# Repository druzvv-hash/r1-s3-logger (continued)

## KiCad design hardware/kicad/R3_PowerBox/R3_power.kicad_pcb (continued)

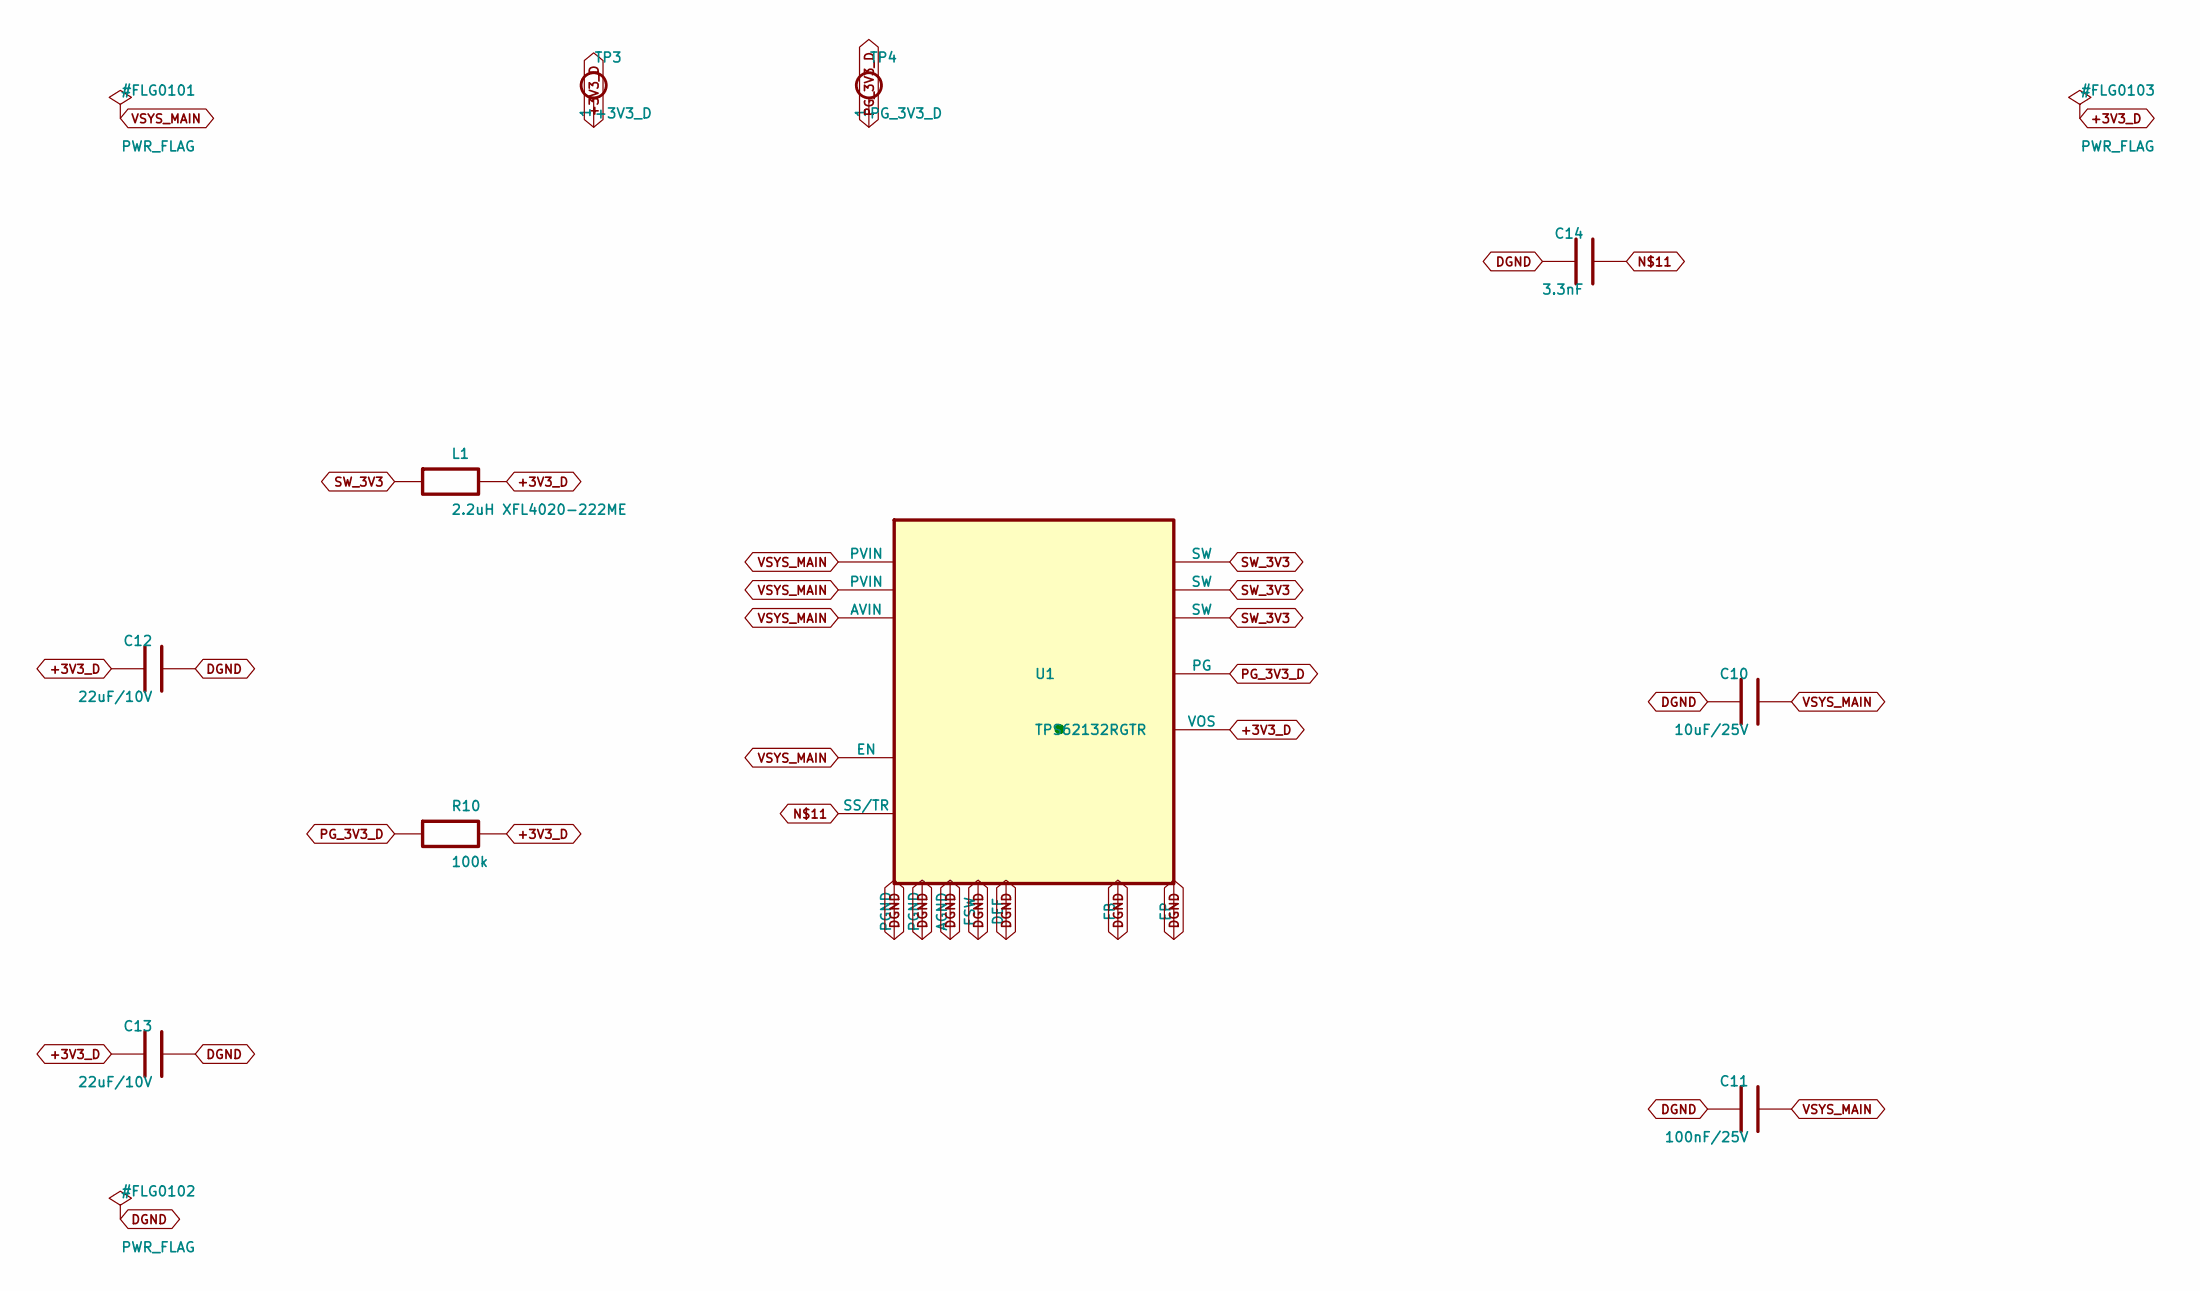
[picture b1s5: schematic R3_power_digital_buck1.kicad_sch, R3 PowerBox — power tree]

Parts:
C10: 10uF/25V; C_1206_3216Metric
C11: 100nF/25V; C_0603_1608Metric
C12, C13: 22uF/10V; C_0805_2012Metric
C14: 3.3nF; C_0603_1608Metric
L1: 2.2uH XFL4020-222ME; L_Coilcraft_XFL4020
R10: 100k; R_0603_1608Metric
TP3: +3V3_D; TestPoint_Plated_Hole_D2.0mm
TP4: PG_3V3_D; TestPoint_Plated_Hole_D2.0mm
U1: TPS62132RGTR; VQFN-16-1EP_3x3mm_P0.5mm_EP1.45x1.45mm

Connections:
+3V3_D: C12.1, C13.1, L1.2, R10.2, TP3.1, U1.14 (VOS); also elsewhere on the board
DGND: C10.2, C11.2, C12.2, C13.2, C14.2, U1.5 (FB), U1.6 (AGND), U1.7 (FSW), U1.8 (DEF), U1.15 (PGND), U1.16 (PGND), U1.17 (EP); also elsewhere on the board
unnamed: C14.1, U1.9 (SS/TR)
PG_3V3_D: R10.1, TP4.1, U1.4 (PG); also elsewhere on the board
SW_3V3: L1.1, U1.1 (SW), U1.2 (SW), U1.3 (SW)
VSYS_MAIN: C10.1, C11.1, U1.10 (AVIN), U1.11 (PVIN), U1.12 (PVIN), U1.13 (EN); also elsewhere on the board

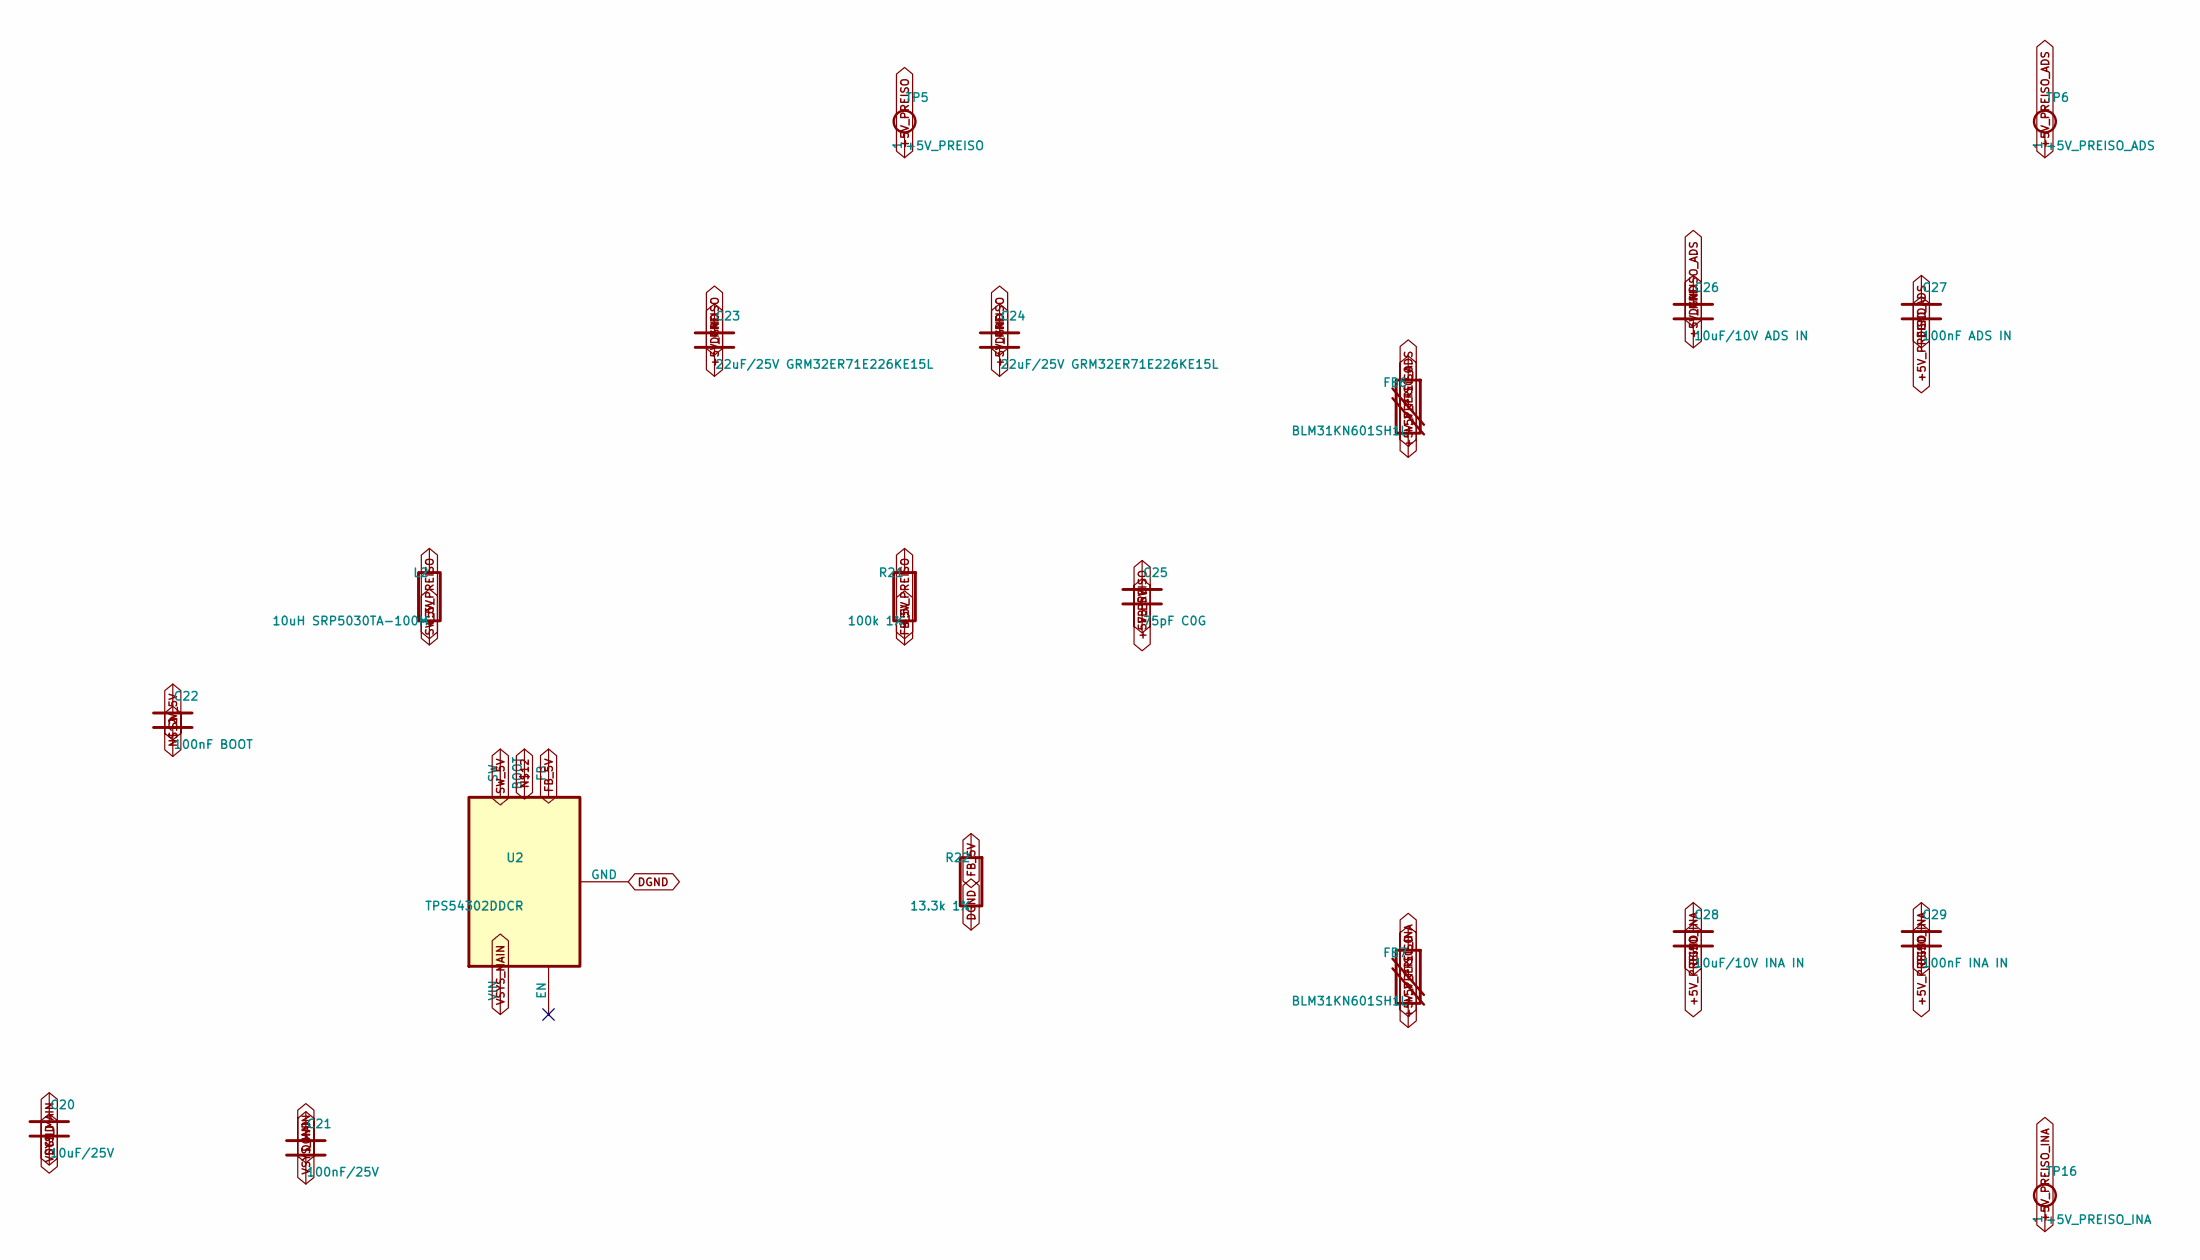
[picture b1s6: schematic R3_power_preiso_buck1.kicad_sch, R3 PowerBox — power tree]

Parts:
C20: 10uF/25V; C_1206_3216Metric
C21: 100nF/25V; C_0603_1608Metric
C22: 100nF BOOT; C_0603_1608Metric
C23, C24: 22uF/25V GRM32ER71E226KE15L; C_1210_3225Metric
C25: 75pF C0G; C_0603_1608Metric
C26: 10uF/10V ADS IN; C_0805_2012Metric
C27: 100nF ADS IN; C_0603_1608Metric
C28: 10uF/10V INA IN; C_0805_2012Metric
C29: 100nF INA IN; C_0603_1608Metric
FB6, FB7: BLM31KN601SH1L; L_1206_3216Metric_Pad1.22x1.90mm_HandSolder
L2: 10uH SRP5030TA-100M; L_Bourns_SRP5030T
R21: 100k 1%; R_0603_1608Metric
R22: 13.3k 1%; R_0603_1608Metric
TP5: +5V_PREISO; TestPoint_Plated_Hole_D2.0mm
TP6: +5V_PREISO_ADS; TestPoint_Plated_Hole_D2.0mm
TP16: +5V_PREISO_INA; TestPoint_Plated_Hole_D2.0mm
U2: TPS54302DDCR; SOT-23-6

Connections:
+5V_PREISO: C23.1, C24.1, C25.1, FB6.1, FB7.1, L2.2, R21.1, TP5.1
+5V_PREISO_ADS: C26.1, C27.1, FB6.2, TP6.1; also elsewhere on the board
+5V_PREISO_INA: C28.1, C29.1, FB7.2, TP16.1; also elsewhere on the board
DGND: C20.2, C21.2, C23.2, C24.2, C26.2, C27.2, C28.2, C29.2, R22.2, U2.1 (GND); also elsewhere on the board
FB_5V: C25.2, R21.2, R22.1, U2.4 (FB)
unnamed: C22.1, U2.6 (BOOT)
SW_5V: C22.2, L2.1, U2.2 (SW)
VSYS_MAIN: C20.1, C21.1, U2.3 (VIN); also elsewhere on the board

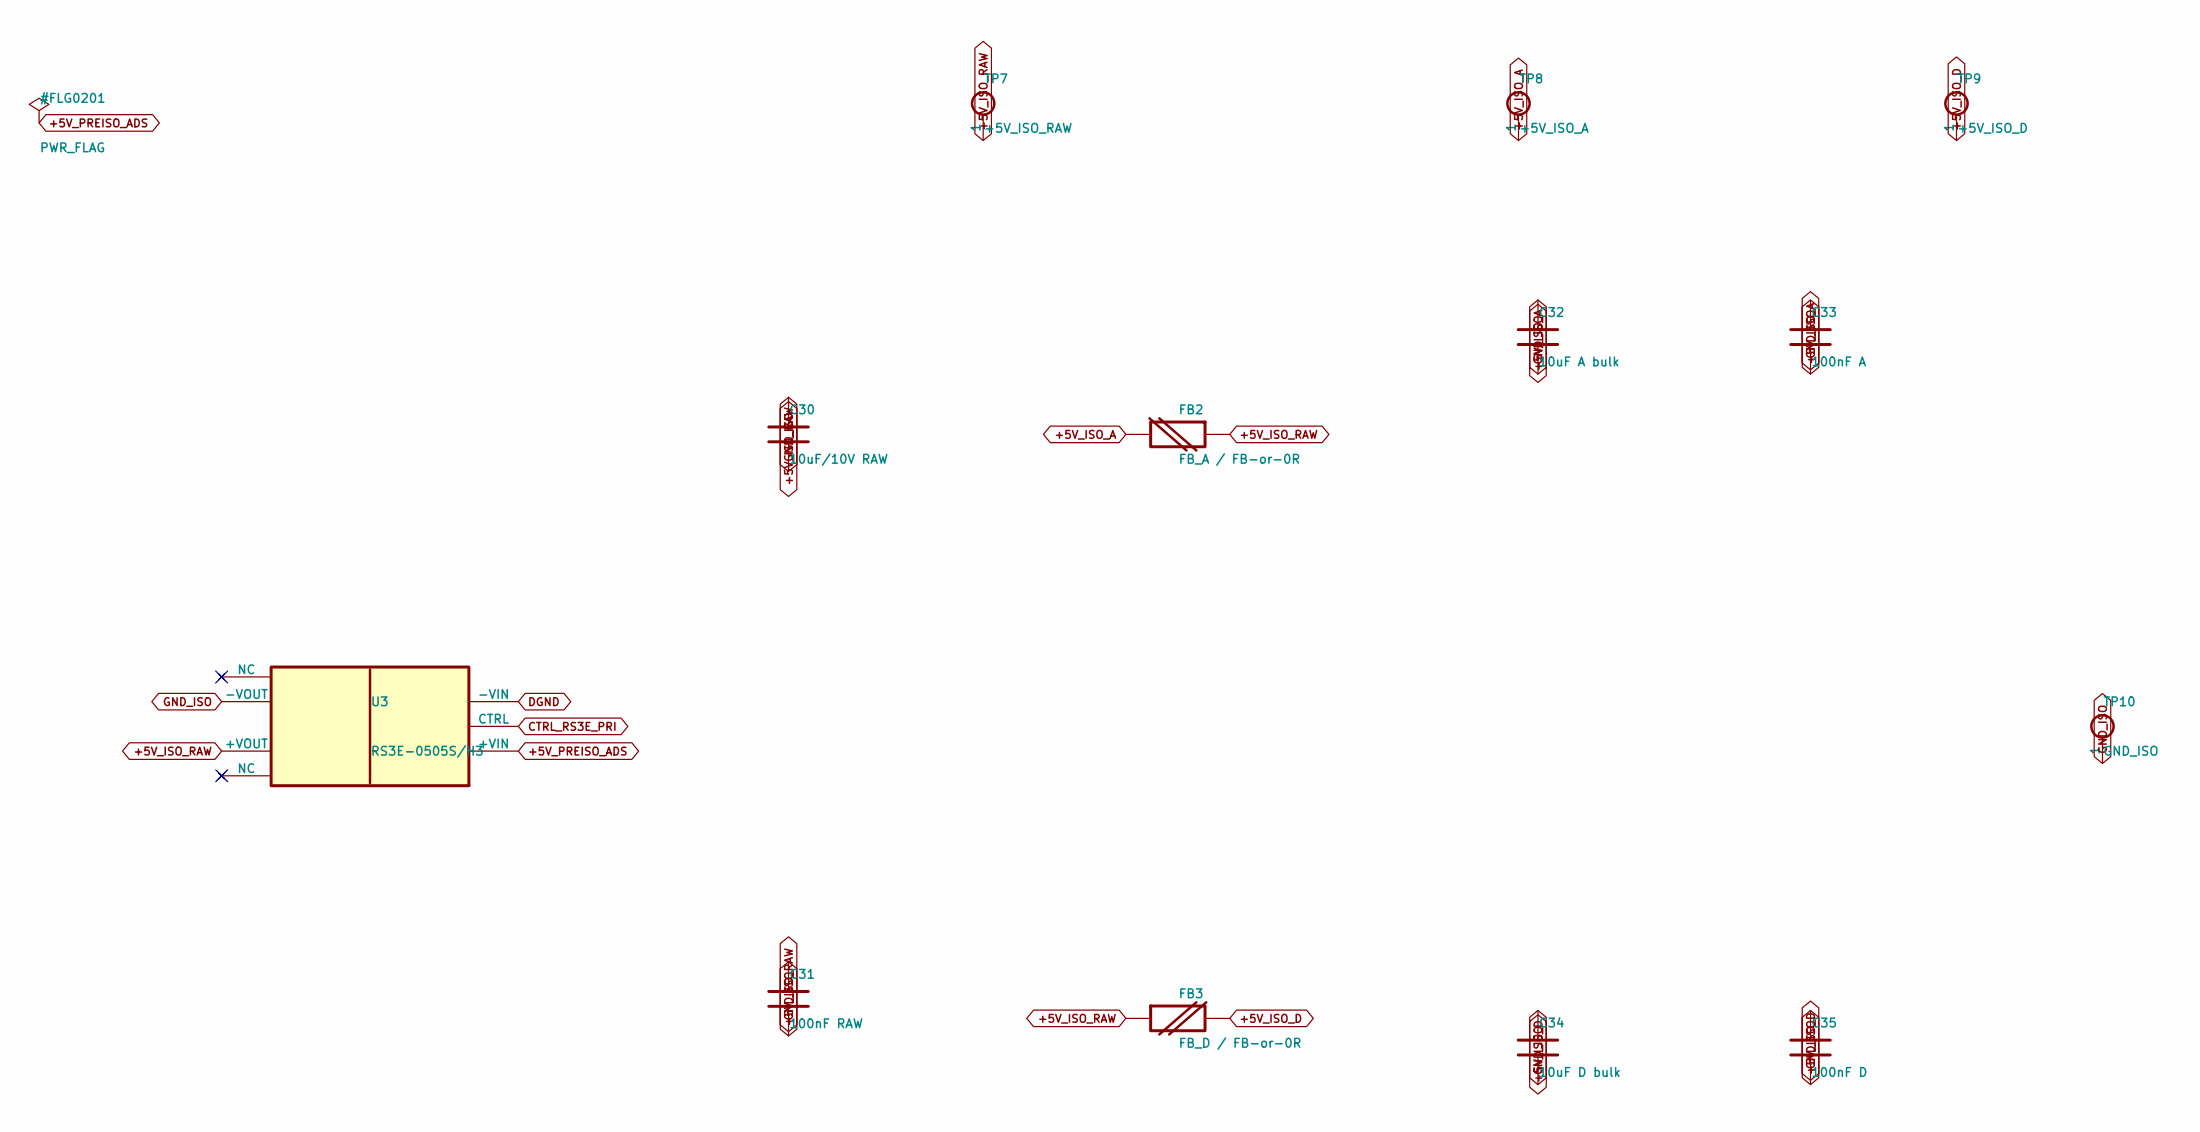
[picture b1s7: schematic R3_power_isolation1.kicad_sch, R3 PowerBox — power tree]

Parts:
C30: 10uF/10V RAW; C_0805_2012Metric
C31: 100nF RAW; C_0603_1608Metric
C32: 10uF A bulk; C_0805_2012Metric
C33: 100nF A; C_0603_1608Metric
C34: 10uF D bulk; C_0805_2012Metric
C35: 100nF D; C_0603_1608Metric
FB2: FB_A / FB-or-0R; R_0805_2012Metric
FB3: FB_D / FB-or-0R; R_0805_2012Metric
TP7: +5V_ISO_RAW; TestPoint_Plated_Hole_D2.0mm
TP8: +5V_ISO_A; TestPoint_Plated_Hole_D2.0mm
TP9: +5V_ISO_D; TestPoint_Plated_Hole_D2.0mm
TP10: GND_ISO; TestPoint_Plated_Hole_D2.0mm
U3: RS3E-0505S/H3; Converter_DCDC_RECOM_RS3E_SIP8

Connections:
+5V_ISO_A: C32.1, C33.1, FB2.2, TP8.1; also elsewhere on the board
+5V_ISO_D: C34.1, C35.1, FB3.2, TP9.1; also elsewhere on the board
+5V_ISO_RAW: C30.1, C31.1, FB2.1, FB3.1, TP7.1, U3.6 (+VOUT); also elsewhere on the board
+5V_PREISO_ADS: U3.2 (+VIN); also elsewhere on the board
CTRL_RS3E_PRI: U3.3 (CTRL); also elsewhere on the board
DGND: U3.1 (-VIN); also elsewhere on the board
GND_ISO: C30.2, C31.2, C32.2, C33.2, C34.2, C35.2, TP10.1, U3.7 (-VOUT); also elsewhere on the board

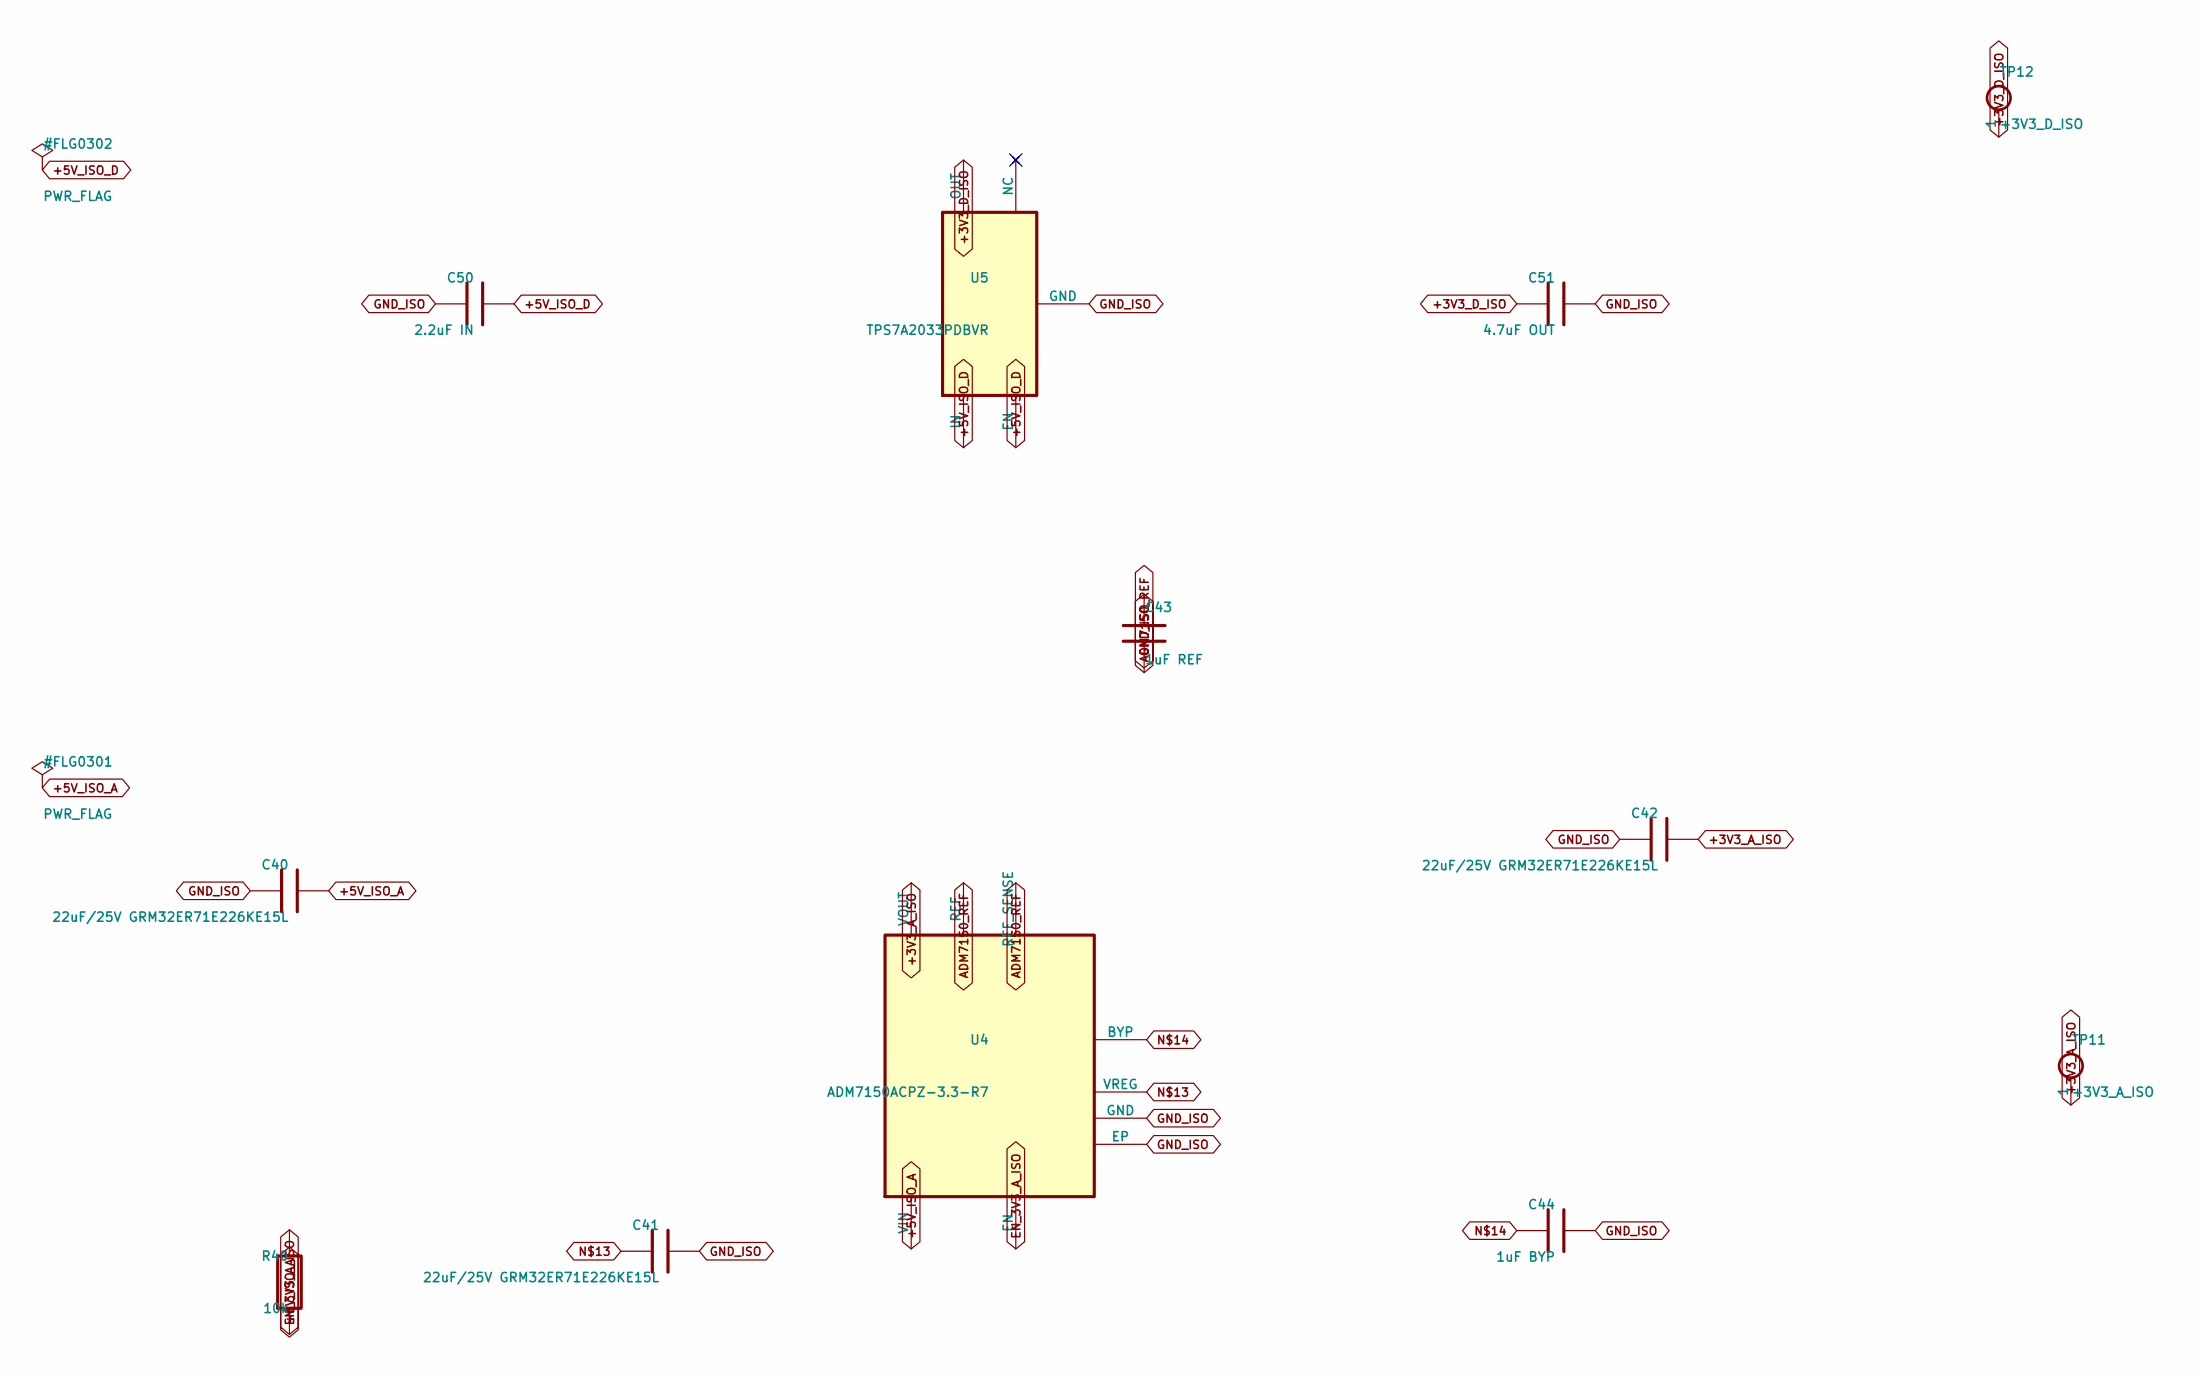
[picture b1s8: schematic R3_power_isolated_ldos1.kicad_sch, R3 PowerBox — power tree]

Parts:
C40, C41, C42: 22uF/25V GRM32ER71E226KE15L; C_1210_3225Metric
C43: 1uF REF; C_0603_1608Metric
C44: 1uF BYP; C_0603_1608Metric
C50: 2.2uF IN; C_0603_1608Metric
C51: 4.7uF OUT; C_0603_1608Metric
R40: 10k; R_0603_1608Metric
TP11: +3V3_A_ISO; TestPoint_Plated_Hole_D2.0mm
TP12: +3V3_D_ISO; TestPoint_Plated_Hole_D2.0mm
U4: ADM7150ACPZ-3.3-R7; LFCSP-8-1EP_3x3mm_P0.5mm_EP1.74x1.45mm
U5: TPS7A2033PDBVR; SOT-23-5

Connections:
+3V3_A_ISO: C42.1, TP11.1, U4.2 (VOUT); also elsewhere on the board
+3V3_D_ISO: C51.1, TP12.1, U5.5 (OUT); also elsewhere on the board
+5V_ISO_A: C40.1, R40.1, U4.8 (VIN); also elsewhere on the board
+5V_ISO_D: C50.1, U5.1 (IN), U5.3 (EN); also elsewhere on the board
ADM7150_REF: C43.1, U4.5 (REF_SENSE), U4.6 (REF)
EN_3V3_A_ISO: R40.2, U4.7 (EN)
GND_ISO: C40.2, C41.2, C42.2, C43.2, C44.2, C50.2, C51.2, U4.4 (GND), U4.9 (EP), U5.2 (GND); also elsewhere on the board
unnamed: C41.1, U4.1 (VREG)
unnamed: C44.1, U4.3 (BYP)

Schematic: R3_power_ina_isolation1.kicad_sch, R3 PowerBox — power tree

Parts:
C60: 10uF +5V bulk; C_0805_2012Metric
C61: 100nF +5V; C_0603_1608Metric
C62: 10uF -5V bulk; C_0805_2012Metric
C63: 100nF -5V; C_0603_1608Metric
FB4, FB5: 0R / FB / L BENCH SELECT; L_1206_3216Metric_Pad1.22x1.90mm_HandSolder
R107, R108: DNP PRELOAD / BENCH SELECT; R_2512_6332Metric; not fitted
TP13: +5V_INA; TestPoint_Plated_Hole_D2.0mm
TP14: -5V_INA; TestPoint_Plated_Hole_D2.0mm
U6: RS3-0505D/H3; Converter_DCDC_RECOM_RS3_SIP8

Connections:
+5V_INA: C60.1, C61.1, FB4.2, R107.1, TP13.1; also elsewhere on the board
+5V_INA_RAW: FB4.1, U6.6 (+VOUT)
+5V_PREISO_INA: U6.2 (+VIN); also elsewhere on the board
-5V_INA: C62.2, C63.2, FB5.2, R108.1, TP14.1; also elsewhere on the board
-5V_INA_RAW: FB5.1, U6.8 (-VOUT)
DGND: U6.1 (-VIN); also elsewhere on the board
GND_ISO: C60.2, C61.2, C62.1, C63.1, R107.2, R108.2, U6.7 (COM); also elsewhere on the board

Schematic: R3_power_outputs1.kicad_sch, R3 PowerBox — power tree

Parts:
D6: LTST-C190KGKT GREEN / RUN; LED_0603_1608Metric
J2: DIGITAL POWER OUT; Molex_Micro-Fit_3.0_43650-0600_1x06_P3.00mm_Horizontal
J3: ISOLATED POWER OUT; Molex_Micro-Fit_3.0_43650-1000_1x10_P3.00mm_Horizontal
J4: CONTROL / SERVICE; Molex_Micro-Fit_3.0_43650-0400_1x04_P3.00mm_Horizontal
J5: PRIMARY AUX DNP; JST_GH_SM04B-GHS-TB_1x04-1MP_P1.25mm_Horizontal; not fitted
J6: ISOLATED AUX DNP; JST_GH_SM04B-GHS-TB_1x04-1MP_P1.25mm_Horizontal; not fitted
J10: BATTERY / CHARGER TELEMETRY; Molex_Micro-Fit_3.0_43650-1000_1x10_P3.00mm_Horizontal
J11: USER PANEL / PRIMARY ONLY; Molex_Micro-Fit_3.0_43650-1000_1x10_P3.00mm_Horizontal
J12: PRIMARY B2B 2x8 / DNP; PinHeader_2x08_P2.54mm_Vertical; not fitted
J13: ISOLATED B2B 2x5 / DNP; PinHeader_2x05_P2.54mm_Vertical; not fitted
R105: 2.2k RUN LED / ~0.7mA; R_0603_1608Metric
TP15: DGND; TestPoint_Plated_Hole_D2.0mm

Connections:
+3V3_A_ISO: J3.3, J6.2, J13.3; also elsewhere on the board
+3V3_D: J2.1, J2.2, J5.1, J10.1, J11.1, J12.1, J12.2, R105.1; also elsewhere on the board
+3V3_D_ISO: J3.5, J6.1, J13.5; also elsewhere on the board
+5V_INA: J3.7, J13.7; also elsewhere on the board
+5V_ISO_RAW: J3.1, J13.1; also elsewhere on the board
-5V_INA: J3.9, J13.9; also elsewhere on the board
BQ_STAT_RAW: J11.9; also elsewhere on the board
CHARGER_INT_FAULT: J10.7, J12.9; also elsewhere on the board
CHARGE_STATUS: J10.5, J11.5, J12.8; also elsewhere on the board
CTRL_RS3E_PRI: J4.3; also elsewhere on the board
DGND: D6.1 (K), J2.3, J2.4, J4.1, J5.2, J10.2, J11.2, J12.3, J12.4, TP15.1; also elsewhere on the board
GND_ISO: J3.2, J3.4, J3.6, J3.8, J3.10, J6.3, J13.2, J13.4, J13.6, J13.8, J13.10; also elsewhere on the board
INPUT_SOURCE_STATUS: J10.8, J12.10; also elsewhere on the board
PD_ALERT_N: J10.9, J12.11; also elsewhere on the board
PD_CONTRACT_12V_N: J10.10, J12.12; also elsewhere on the board
PG_3V3_D: J2.5, J4.2, J10.6, J11.6, J12.7; also elsewhere on the board
PM_I2C_SCL: J10.3, J11.7, J12.5; also elsewhere on the board
PM_I2C_SDA: J10.4, J11.8, J12.6; also elsewhere on the board
POWER_CTRL: J11.3, J12.13; also elsewhere on the board
QON_SERVICE: J11.4, J12.14; also elsewhere on the board
RUN_LED_A: D6.2 (A), R105.2

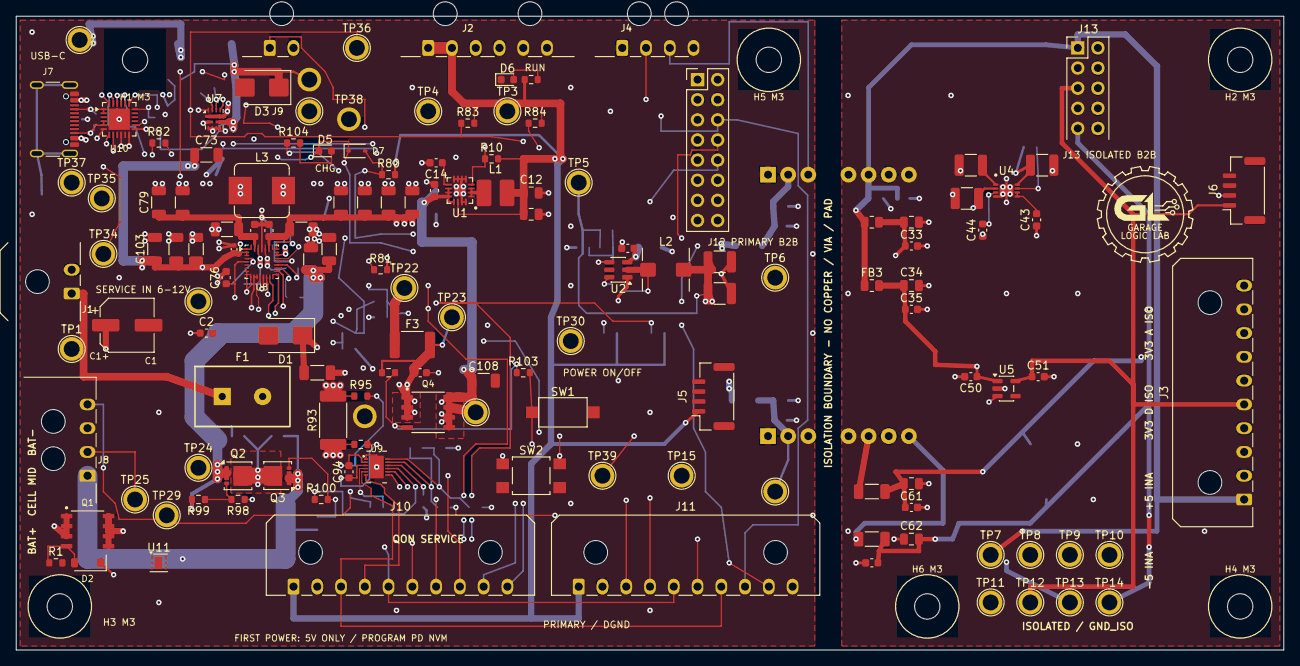
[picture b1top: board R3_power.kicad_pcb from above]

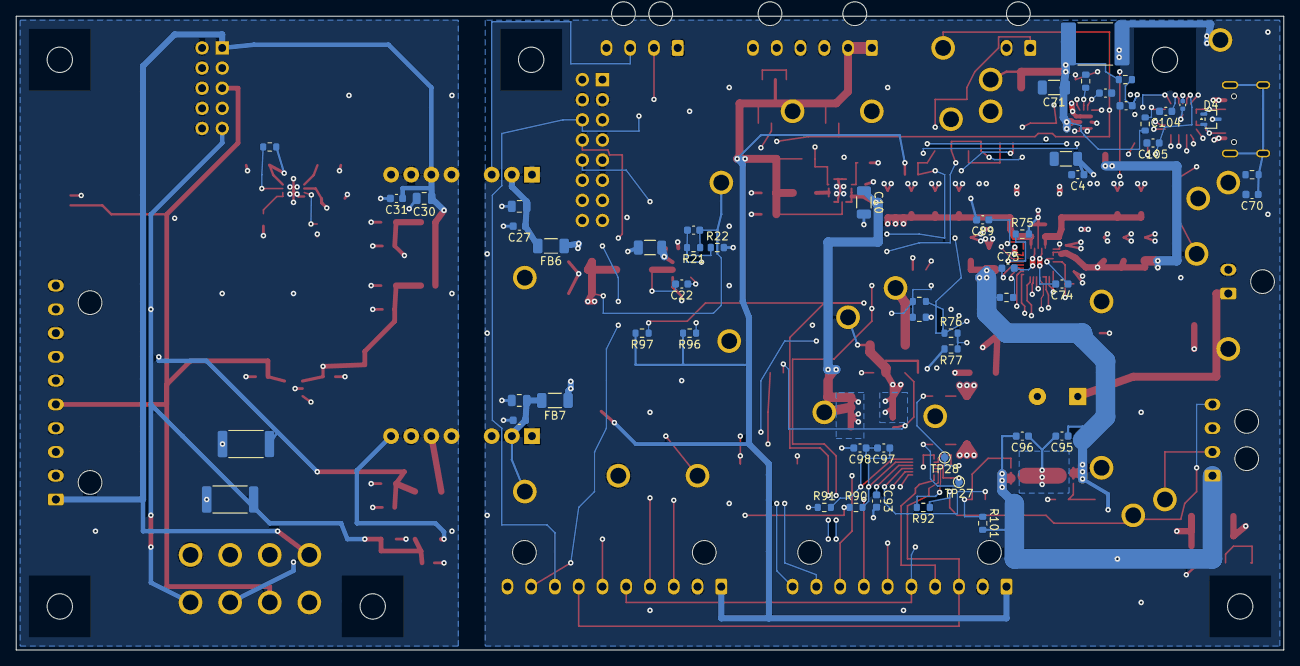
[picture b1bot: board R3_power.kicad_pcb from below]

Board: 4 copper layers, 160.0 x 80.0 mm, 203 parts (54 on the bottom side), 86 nets.

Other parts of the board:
H1, H2, H3, H4, H5, H6: M3 NPTH 3.2mm / 8mm KEEPOUT; MountingHole_M3_NPTH_3.2mm_Keepout8mm

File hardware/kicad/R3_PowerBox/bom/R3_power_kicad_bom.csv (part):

"Refs","Value","Footprint","Qty","DNP"
"C1","47uF/25V low-ESR","Capacitor_SMD:CP_Elec_6.3x5.8","1",""
"C2","100nF/25V","Capacitor_SMD:C_0603_1608Metric","1",""
"C3","22uF/25V","Capacitor_SMD:C_1206_3216Metric","1",""
"C4","100nF/25V","Capacitor_SMD:C_0603_1608Metric","1",""
"C10","10uF/25V","Capacitor_SMD:C_1206_3216Metric","1",""
"C11","100nF/25V","Capacitor_SMD:C_0603_1608Metric","1",""
"C12","22uF/10V","Capacitor_SMD:C_0805_2012Metric","1",""
"C13","22uF/10V","Capacitor_SMD:C_0805_2012Metric","1",""
"C14","3.3nF","Capacitor_SMD:C_0603_1608Metric","1",""
"C20","10uF/25V","Capacitor_SMD:C_1206_3216Metric","1",""
"C21","100nF/25V","Capacitor_SMD:C_0603_1608Metric","1",""
"C22","100nF BOOT","Capacitor_SMD:C_0603_1608Metric","1",""
"C23","22uF/25V GRM32ER71E226KE15L","Capacitor_SMD:C_1210_3225Metric","1",""
"C24","22uF/25V GRM32ER71E226KE15L","Capacitor_SMD:C_1210_3225Metric","1",""
"C25","75pF C0G","Capacitor_SMD:C_0603_1608Metric","1",""
"C26","10uF/10V ADS IN","Capacitor_SMD:C_0805_2012Metric","1",""
"C27","100nF ADS IN","Capacitor_SMD:C_0603_1608Metric","1",""
"C28","10uF/10V INA IN","Capacitor_SMD:C_0805_2012Metric","1",""
"C29","100nF INA IN","Capacitor_SMD:C_0603_1608Metric","1",""
"C30","10uF/10V RAW","Capacitor_SMD:C_0805_2012Metric","1",""
"C31","100nF RAW","Capacitor_SMD:C_0603_1608Metric","1",""
"C32","10uF A bulk","Capacitor_SMD:C_0805_2012Metric","1",""
"C33","100nF A","Capacitor_SMD:C_0603_1608Metric","1",""
"C34","10uF D bulk","Capacitor_SMD:C_0805_2012Metric","1",""
"C35","100nF D","Capacitor_SMD:C_0603_1608Metric","1",""
"C40","22uF/25V GRM32ER71E226KE15L","Capacitor_SMD:C_1210_3225Metric","1",""
"C41","22uF/25V GRM32ER71E226KE15L","Capacitor_SMD:C_1210_3225Metric","1",""
"C42","22uF/25V GRM32ER71E226KE15L","Capacitor_SMD:C_1210_3225Metric","1",""
"C43","1uF REF","Capacitor_SMD:C_0603_1608Metric","1",""
"C44","1uF BYP","Capacitor_SMD:C_0603_1608Metric","1",""
"C50","2.2uF IN","Capacitor_SMD:C_0603_1608Metric","1",""
"C51","4.7uF OUT","Capacitor_SMD:C_0603_1608Metric","1",""
"C60","10uF +5V bulk","Capacitor_SMD:C_0805_2012Metric","1",""
"C61","100nF +5V","Capacitor_SMD:C_0603_1608Metric","1",""
"C62","10uF -5V bulk","Capacitor_SMD:C_0805_2012Metric","1",""
"C63","100nF -5V","Capacitor_SMD:C_0603_1608Metric","1",""
"C70","4.7nF SHIELD","Capacitor_SMD:C_0603_1608Metric","1",""
"C71","4.7uF/25V USB","Capacitor_SMD:C_1206_3216Metric","1",""
"C72","100nF MUX SS","Capacitor_SMD:C_0603_1608Metric","1",""
"C73","10uF/25V MUX OUT","Capacitor_SMD:C_1206_3216Metric","1",""
"C74","47nF BTST1","Capacitor_SMD:C_0603_1608Metric","1",""
"C75","47nF BTST2","Capacitor_SMD:C_0603_1608Metric","1",""
"C76","4.7uF REGN","Capacitor_SMD:C_0603_1608Metric","1",""
"C77","10uF/25V PMID","Capacitor_SMD:C_1206_3216Metric","1",""
"C78","10uF/25V PMID","Capacitor_SMD:C_1206_3216Metric","1",""
"C79","10uF/25V PMID","Capacitor_SMD:C_1206_3216Metric","1",""
"C80","100nF PMID","Capacitor_SMD:C_0603_1608Metric","1",""
"C81","10uF/16V SYS","Capacitor_SMD:C_1206_3216Metric","1",""
"C82","10uF/16V SYS","Capacitor_SMD:C_1206_3216Metric","1",""
"C83","10uF/16V SYS","Capacitor_SMD:C_1206_3216Metric","1",""
"C84","10uF/16V SYS","Capacitor_SMD:C_1206_3216Metric","1",""
"C85","10uF/16V SYS","Capacitor_SMD:C_1206_3216Metric","1",""
"C86","100nF SYS","Capacitor_SMD:C_0603_1608Metric","1",""
"C87","10uF/16V BAT","Capacitor_SMD:C_1206_3216Metric","1",""
"C88","10uF/16V BAT","Capacitor_SMD:C_1206_3216Metric","1",""
"C89","1nF/50V C0G SDRV","Capacitor_SMD:C_0603_1608Metric","1",""
"C93","2.2uF PBI","Capacitor_SMD:C_0603_1608Metric","1",""
"C94","100nF SHUNT DIFF","Capacitor_SMD:C_0603_1608Metric","1",""
"C95","100nF DSG D-S / TI EVM","Capacitor_SMD:C_0603_1608Metric","1",""
"C96","100nF CHG D-S / TI EVM","Capacitor_SMD:C_0603_1608Metric","1",""
"C97","100nF VC2-VC1 / CELL2","Capacitor_SMD:C_0603_1608Metric","1",""
"C98","100nF VC1-VSS / CELL1","Capacitor_SMD:C_0603_1608Metric","1",""
"C100","100nF/25V VBUS LOCAL","Capacitor_SMD:C_0402_1005Metric","1",""
"C101","10uF/25V VBUS LOCAL","Capacitor_SMD:C_1206_3216Metric","1",""
"C102","10uF/25V VBUS LOCAL","Capacitor_SMD:C_1206_3216Metric","1",""
"C103","10uF/25V VBUS LOCAL","Capacitor_SMD:C_1206_3216Metric","1",""
"C104","1uF VREG_1V2","Capacitor_SMD:C_0603_1608Metric","1",""
"C105","1uF VREG_2V7","Capacitor_SMD:C_0603_1608Metric","1",""
"C106","1uF/25V PD VDD","Capacitor_SMD:C_0603_1608Metric","1",""
"C107","100nF G-S / SOFT START","Capacitor_SMD:C_0603_1608Metric","1",""
"C108","10uF/16V VSYS_MAIN","Capacitor_SMD:C_1206_3216Metric","1",""
"C109","1uF/10V PD VSYS","Capacitor_SMD:C_0402_1005Metric","1",""
"D1","SMBJ13A / 13V VRWM","Diode_SMD:D_SMB","1",""
"D2","BZT52C10","Diode_SMD:D_SOD-123","1",""
"D3","SMBJ13A / 13V VRWM USB VBUS","Diode_SMD:D_SMB","1",""
"D4","ESDA25W CC ESD / P1,P2=CC P3=GND","Package_TO_SOT_SMD:SOT-323_SC-70","1",""
"D5","LTST-C190KRKT RED / CHG","LED_SMD:LED_0603_1608Metric","1",""
"D6","LTST-C190KGKT GREEN / RUN","LED_SMD:LED_0603_1608Metric","1",""
"D7","BAT54WS-7-F STAT ISOLATION","Diode_SMD:D_SOD-323","1",""
"F1","MF-R250-0-10 2.5A/30V PPTC","R3_Power:Fuse_PTC_MF-R250","1",""
"F2","2920L260/33DR 2.6A/33V","Fuse:Fuse_2920_7451Metric","1",""
"F3","MF-MSMF250/16X-2 2.5A/16V PPTC","Fuse:Fuse_1812_4532Metric_Pad1.30x3.40mm_HandSolder","1",""
"FB1","BLM31KN121SN1L / 6A","Inductor_SMD:L_1206_3216Metric_Pad1.22x1.90mm_HandSolder","1",""
"FB2","FB_A / FB-or-0R","Resistor_SMD:R_0805_2012Metric","1",""
"FB3","FB_D / FB-or-0R","Resistor_SMD:R_0805_2012Metric","1",""
"FB4","0R / FB / L BENCH SELECT","Inductor_SMD:L_1206_3216Metric_Pad1.22x1.90mm_HandSolder","1",""
"FB5","0R / FB / L BENCH SELECT","Inductor_SMD:L_1206_3216Metric_Pad1.22x1.90mm_HandSolder","1",""
"FB6","BLM31KN601SH1L","Inductor_SMD:L_1206_3216Metric_Pad1.22x1.90mm_HandSolder","1",""
"FB7","BLM31KN601SH1L","Inductor_SMD:L_1206_3216Metric_Pad1.22x1.90mm_HandSolder","1",""
"J1","SERVICE / BENCH INPUT 6-12V","Connector_Molex:Molex_Micro-Fit_3.0_43650-0200_1x02_P3.00mm_Horizontal","1",""
"J2","DIGITAL POWER OUT","Connector_Molex:Molex_Micro-Fit_3.0_43650-0600_1x06_P3.00mm_Horizontal","1",""
"J3","ISOLATED POWER OUT","Connector_Molex:Molex_Micro-Fit_3.0_43650-1000_1x10_P3.00mm_Horizontal","1",""
"J4","CONTROL / SERVICE","Connector_Molex:Molex_Micro-Fit_3.0_43650-0400_1x04_P3.00mm_Horizontal","1",""
"J5","PRIMARY AUX DNP","Connector_JST:JST_GH_SM04B-GHS-TB_1x04-1MP_P1.25mm_Horizontal","1","DNP"
"J6","ISOLATED AUX DNP","Connector_JST:JST_GH_SM04B-GHS-TB_1x04-1MP_P1.25mm_Horizontal","1","DNP"
"J7","USB4105-GF-A","Connector_USB:USB_C_Receptacle_GCT_USB4105-xx-A_16P_TopMnt_Horizontal","1",""
"J8","2S BATTERY / KEYED / NTC_BMS=103AT-2","Connector_Molex:Molex_Micro-Fit_3.0_43650-0400_1x04_P3.00mm_Horizontal","1",""
"J9","NTC_CHG=103AT-2 / QUIET DGND RETURN","Connector_Molex:Molex_Micro-Fit_3.0_43650-0200_1x02_P3.00mm_Horizontal","1",""
"J10","BATTERY / CHARGER TELEMETRY","Connector_Molex:Molex_Micro-Fit_3.0_43650-1000_1x10_P3.00mm_Horizontal","1",""
"J11","USER PANEL / PRIMARY ONLY","Connector_Molex:Molex_Micro-Fit_3.0_43650-1000_1x10_P3.00mm_Horizontal","1",""
"J12","PRIMARY B2B 2x8 / DNP","Connector_PinHeader_2.54mm:PinHeader_2x08_P2.54mm_Vertical","1","DNP"
"J13","ISOLATED B2B 2x5 / DNP","Connector_PinHeader_2.54mm:PinHeader_2x05_P2.54mm_Vertical","1","DNP"
"L1","2.2uH XFL4020-222ME","R3_Power:L_Coilcraft_XFL4020","1",""
"L2","10uH SRP5030TA-100M","Inductor_SMD:L_Bourns_SRP5030T","1",""
"L3","SRP7028A-1R0M 1uH","Inductor_SMD:L_Bourns_SRP7028A_7.3x6.6mm","1",""
"Q1","DMP3007LSS-13","R3_Power:DMP3007LSS_SO8_LOGICAL","1",""
"Q2","CSD17577Q3AT 30V NMOS DSG","R3_Power:CSD17577Q3A_VSON-8_3.3x3.3mm","1",""
"Q3","CSD17577Q3AT 30V NMOS CHG","R3_Power:CSD17577Q3A_VSON-8_3.3x3.3mm","1",""
"Q4","DMP3007LSS-13 SYSTEM LOAD SWITCH","R3_Power:DMP3007LSS_SO8_LOGICAL","1",""
"R1","100k","Resistor_SMD:R_0603_1608Metric","1",""
"R10","100k","Resistor_SMD:R_0603_1608Metric","1",""
"R21","100k 1%","Resistor_SMD:R_0603_1608Metric","1",""
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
